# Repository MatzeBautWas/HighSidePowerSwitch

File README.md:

# HighSidePowerSwitch
Magnetic controlled electronical power switch for rc- models such as submarines

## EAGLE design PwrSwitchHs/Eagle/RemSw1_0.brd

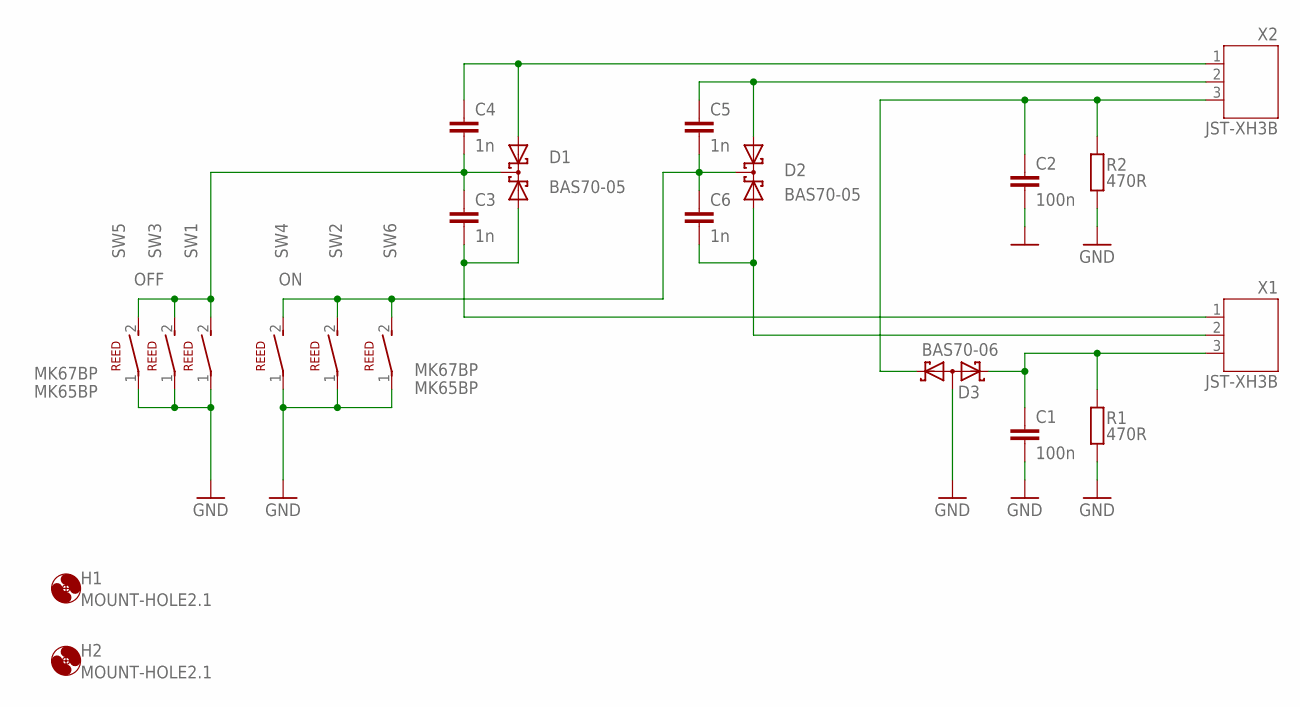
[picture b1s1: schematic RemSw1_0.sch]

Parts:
C1, C2: 100n; C0805
C3, C4, C5, C6: 1n; C0805
D1, D2: BAS70-05; SOT23
D3: BAS70-06; SOT23
H1, H2: MOUNT-HOLE2.1; 2,1
R1, R2: 470R; R0805
SW1: OFF; KSK1A66
SW2: ON; KSK1A66
SW3, SW6: MK67BP; MK67-BP
SW4, SW5: MK65BP; MK65-BP
X1, X2: JST-XH3B; B3B-XH

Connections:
GND: C1.2, C2.2, D3.3 (AA), R1.1, R2.1, SW1.1, SW2.1, SW3.1, SW4.1, SW5.1, SW6.1
unnamed: C2.1, D3.1 (K1), R2.2, X2.3
unnamed: C1.1, D3.2 (K2), R1.2, X1.3
unnamed: C5.1, D2.1 (A1), X2.2
unnamed: C4.1, D1.2 (A2), X2.1
unnamed: C6.2, D2.2 (A2), X1.2
unnamed: C3.2, D1.1 (A1), X1.1
OFF: C3.1, C4.2, D1.3 (C), SW1.2, SW3.2, SW5.2
ON: C5.2, C6.1, D2.3 (C), SW2.2, SW4.2, SW6.2

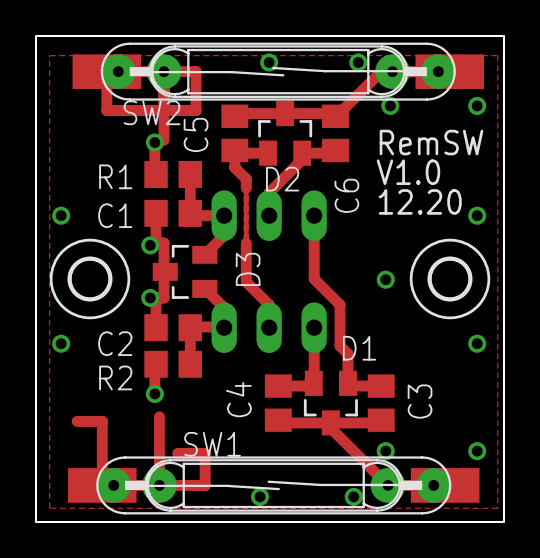
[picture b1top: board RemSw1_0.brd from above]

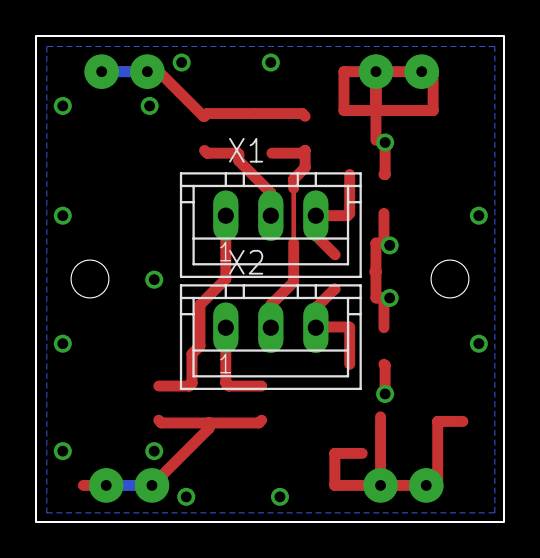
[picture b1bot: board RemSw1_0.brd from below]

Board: 2 copper layers, 26.0 x 27.0 mm, 21 parts (2 on the bottom side), 9 nets.

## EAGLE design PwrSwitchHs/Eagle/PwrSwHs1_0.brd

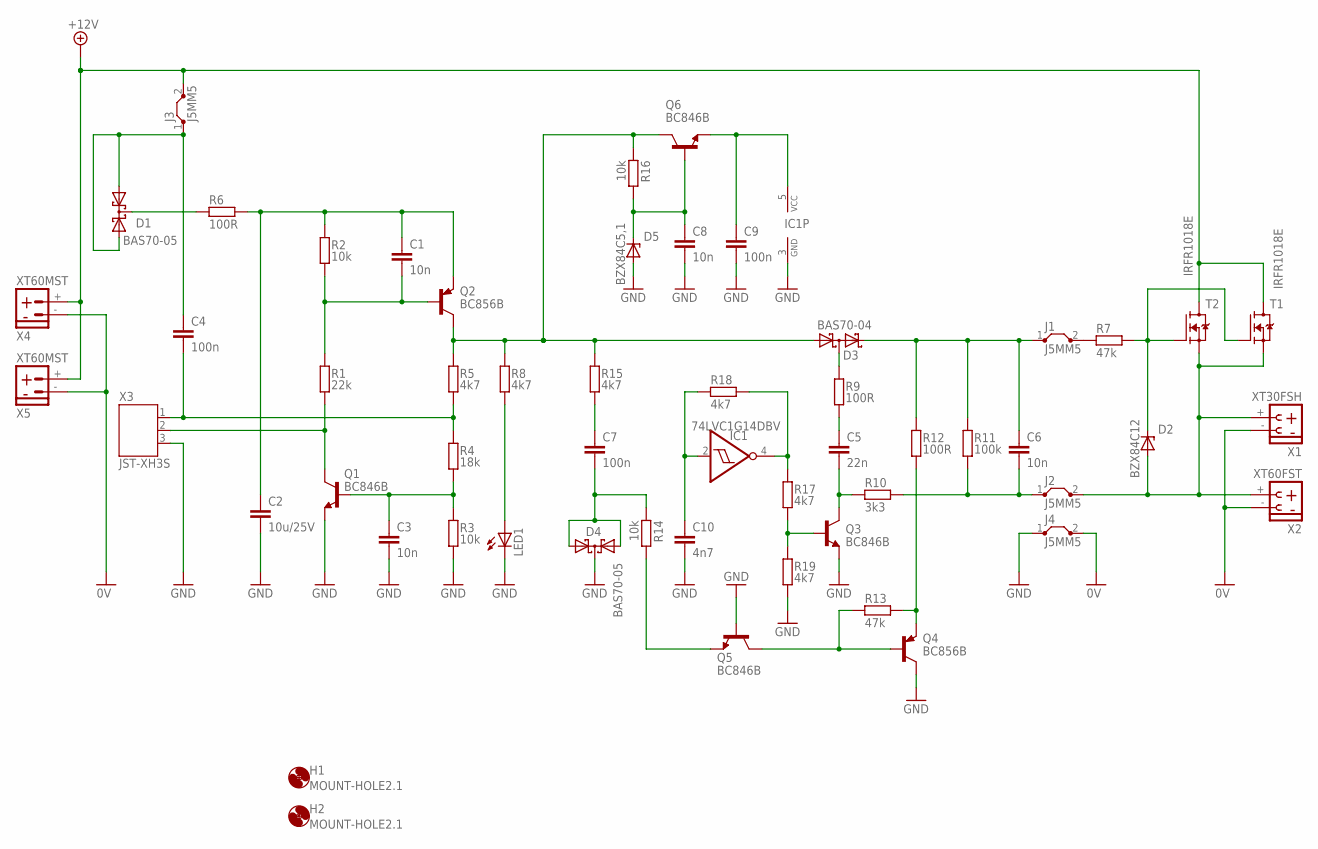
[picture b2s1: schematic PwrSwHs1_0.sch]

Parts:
C1, C3, C6, C8: 10n; C0805
C2: 10u/25V; C1210
C4, C7, C9: 100n; C0805
C5: 22n; C0805
C10: 4n7; C0805
D1, D4: BAS70-05; SOT23
D2: BZX84C12; TO236
D3: BAS70-04; SOT23
D5: BZX84C5,1; TO236
H1, H2: MOUNT-HOLE2.1; 2,1
IC1: 74LVC1G14DBV; SOT23-5
J1, J2, J3, J4: J5MM5; 053
LED1: LEDLED3MML; LED3MML
Q1, Q3, Q5, Q6: BC846B; SOT23
Q2, Q4: BC856B; SOT23-BEC
R1: 22k; R0805
R2, R3, R14, R16: 10k; R0805
R4: 18k; R0805
R5, R8, R15, R17, R18, R19: 4k7; R0805
R6, R9, R12: 100R; R0805
R7, R13: 47k; R0805
R10: 3k3; R0805
R11: 100k; R0805
T1, T2: IRFR1018E; TO252
X1: XT30FSH; XT30F-SH
X2: XT60FST; XT60F-ST
X3: JST-XH3S; JST-XH3SMD
X4, X5: XT60MST; XT60M-ST

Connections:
0V: J4.2, X1.-, X2.-, X4.-, X5.-
+4V5: C9.1, IC1.5 (VCC), Q6.2 (E)
+12V: J3.2, T1.3 (D), T2.3 (D), X4.+, X5.+
+12VB: C4.1, D1.1 (A1), D1.2 (A2), J3.1
+12V_SW: D3.1 (A1), Q2.C, Q6.3 (C), R5.2, R8.2, R15.2, R16.1
GATE: C6.1, D3.2 (C2), J1.1, R11.2, R12.2
GATEB: J1.2, R7.1
GATE_LIM: D2.C, R7.2, T1.1 (G), T2.1 (G)
GND: C2.2, C3.2, C8.2, C9.2, C10.2, D4.3 (C), D5.A, IC1.3 (GND), J4.1, LED1.K (C), Q1.2 (E), Q3.2 (E), Q4.C, Q5.1 (B), R3.1, R19.1, X3.3
unnamed: LED1.A, R8.1
unnamed: C5.2, Q3.3 (C), R10.1
unnamed: D3.3 (C1A2), R9.2
unnamed: C5.1, R9.1
unnamed: C1.2, Q2.B, R1.2, R2.1
unnamed: C1.1, C2.1, Q2.E, R2.2, R6.2
unnamed: C3.1, Q1.1 (B), R3.2, R4.1
unnamed: C7.2, D4.1 (A1), D4.2 (A2), R14.1
unnamed: Q3.1 (B), R17.1, R19.2
unnamed: Q4.E, R12.1, R13.2
unnamed: D1.3 (C), R6.1
unnamed: Q4.B, Q5.3 (C), R13.1
unnamed: C7.1, R15.1
unnamed: Q5.2 (E), R14.2
unnamed: C8.1, D5.C, Q6.1 (B), R16.2
unnamed: C10.1, IC1.2 (I), R18.1
unnamed: IC1.4 (O), R17.2, R18.2
OFF: C4.2, R4.2, R5.1, X3.1
ON: Q1.3 (C), R1.1, X3.2
V_OUT: C6.2, J2.1, R10.2, R11.1
V_OUTB: D2.A, J2.2, T1.2 (S), T2.2 (S), X1.+, X2.+

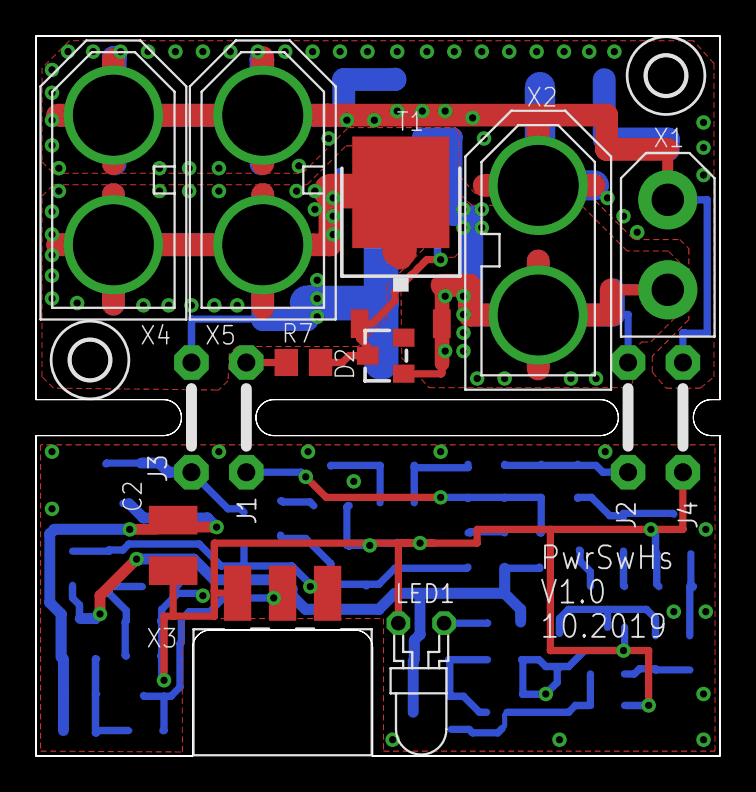
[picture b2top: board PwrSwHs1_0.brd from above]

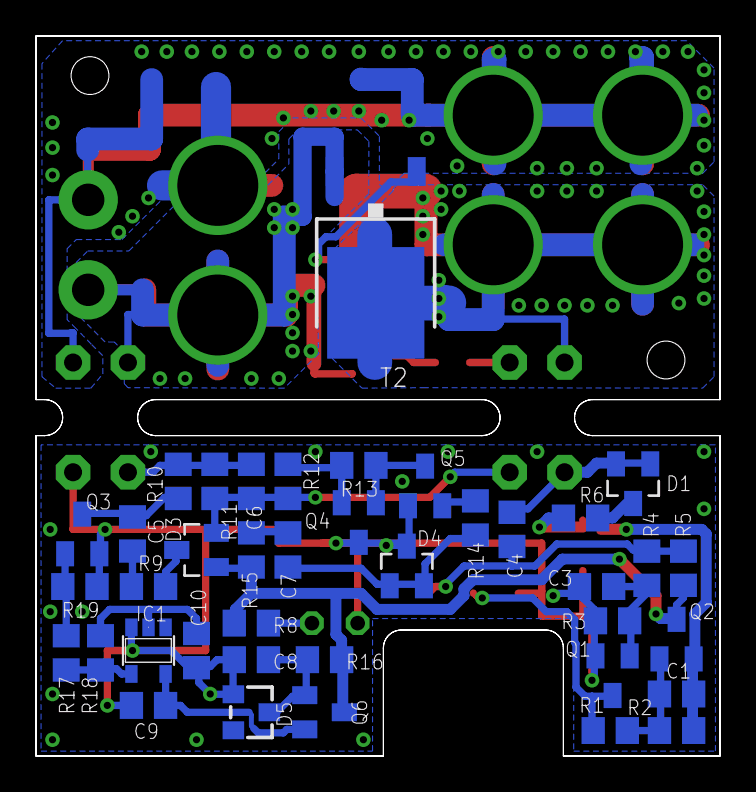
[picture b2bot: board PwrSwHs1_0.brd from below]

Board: 2 copper layers, 38.0 x 40.0 mm, 55 parts (39 on the bottom side), 30 nets.
